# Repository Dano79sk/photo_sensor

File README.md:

Photor sensor based on LM567/LM567C Tone Decoder
PLL phase detector

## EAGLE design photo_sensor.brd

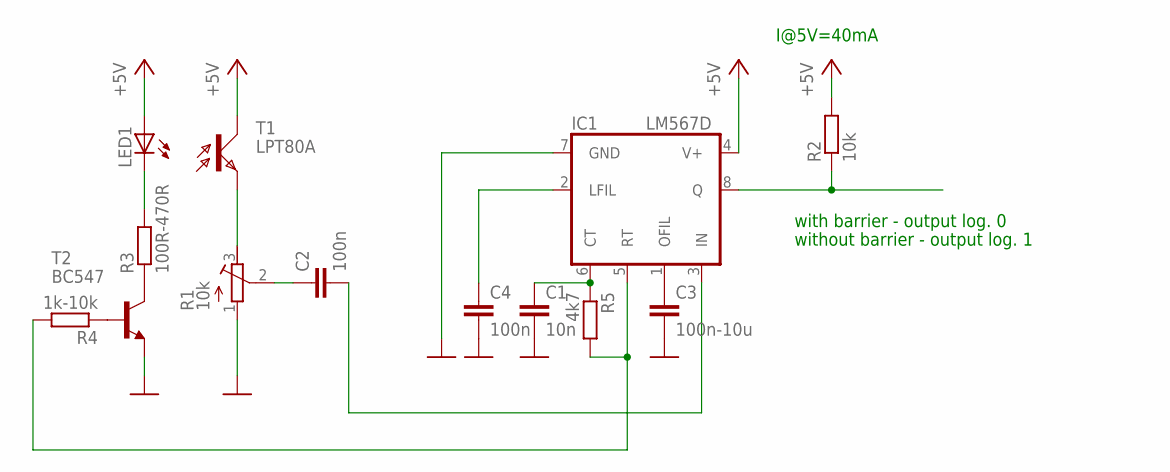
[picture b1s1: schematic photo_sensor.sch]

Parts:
C1: 10n; 0805
C2, C4: 100n; 0805
C3: 100n-10u; 0805
IC1: LM567D; SO08
LED1: LED3MM
R1: 10k; RTRIM3202
R2: 10k; 0805
R3: 100R-470R; 0805
R4: 1k-10k; 0805
R5: 4k7; 0805
T1: LPT80A
T2: BC547; TO92

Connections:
+5V: IC1.4 (V+), LED1.A, R2.2, T1.C
GND: C1.2, C3.2, C4.2, IC1.7 (GND), R1.1 (A), T2.1 (E)
unnamed: R3.1, T2.3 (C)
unnamed: IC1.8 (Q), R2.1
unnamed: LED1.K (C), R3.2
unnamed: R4.1, T2.2 (B)
unnamed: C4.1, IC1.2 (LFIL)
unnamed: IC1.5 (RT), R4.2, R5.2
unnamed: C1.1, IC1.6 (CT), R5.1
unnamed: C3.1, IC1.1 (OFIL)
unnamed: C2.2, IC1.3 (IN)
unnamed: R1.3 (E), T1.E
unnamed: C2.1, R1.2 (S)

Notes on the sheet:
I@5V=40mA
with barrier - output log. 0
without barrier - output log. 1

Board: 2 copper layers, 13 parts (0 on the bottom side), 13 nets, no tracks yet.

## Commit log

2015-11-15 Initial commint, tested schematics, PCB - 0%
2015-11-15 Sdd README.md
